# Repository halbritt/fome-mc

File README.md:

# `fome-mc` — Integrated FOME-Native Motorcycle ECU

For current assembly sourcing, clearance and ignition-copper changes, see the [manufacturing notes](docs/MANUFACTURING.md).

**`fome-mc`** is a single-PCB, 4-layer (`162.0 mm × 115.0 mm`), pottable motorcycle engine control unit running [FOME (`fome-fw`)](https://github.com/halbritt/fome-fw) on an `STM32H753ZIT6` / `STM32H743ZIT6` paired with **two onboard `STM32F042K6T6` Bosch LSU 4.9 wideband controllers**, **four 400 V / 30 A ignition IGBTs**, **four 5 V logic ignition outputs**, **four high-Z injector drivers**, **dual 4-wire stepper drivers (`DRV8825` + `2× TLE9201SG`)**, **dual `MAX9924` adaptive VR conditioners**, **soldered 4 GB industrial SDNAND logging (`CSNP32GCR01-AOW`)**, **onboard `ATWINC1500-MR210UB` U.FL Wi-Fi**, and **dual 35-pin TE Connectivity AMPSEAL (`776163-1` Black & `776163-2` Natural) sealed harness headers**.

The primary reference application is the **2007 Suzuki SV650 (K7)** (`645 cc` 90° V-twin, odd-fire `270° / 450°`, dual spark plugs per cylinder = 4 plugs total, `24-2` crank VR trigger, camless `VVT_MAP_V_TWIN` intake-MAP phase sync, dual 4-wire steppers for `ISC` idle and `STVA` secondary throttle blades, and dual Bosch LSU 4.9 wideband O2 sensors).

---

## Documentation & Visual Index

| Document / Artifact | Description |
| :--- | :--- |
| [**`docs/WIRING_SV650_K7.md`**](docs/WIRING_SV650_K7.md) | Complete 2007 Suzuki SV650 (K7) adapter harness build guide, stock 2×34-pin ECM cavity key, mating TE AMPSEAL connector BOM, pin-by-pin `J1`/`J2` cross-reference, 2-coil vs. 4-coil Primary+Trailing ignition wiring, and dual Bosch LSU 4.9 pinouts |
| [**`docs/POTTING_AND_ENCLOSURE.md`**](docs/POTTING_AND_ENCLOSURE.md) | CNC enclosure stackup, faceplate/bulkhead cutouts, `10.44 W` continuous / `12.74 W` peak thermal dissipation budget, thermal gap-pad coupling, single-pour flood potting (external GM/Delphi 1-bar baro, `FOMEMC-1`), `U29` U.FL RF shield sealing (`FOMEMC-2`), and post-potting DFU recovery |
| [**`docs/TELEMETRY_AND_RACECHRONO.md`**](docs/TELEMETRY_AND_RACECHRONO.md) | `CAN1` motorsport telemetry pod (`ESP32-S3` + `25 Hz` GPS + `Bosch MM5.10` / `BMI088` 6-axis IMU + brake/suspension ADC), `FOME_CAN_verbose.dbc` (`0x200..0x207` @ 50 Hz), RaceChrono Pro BLE DIY integration, and Insta360 / DJI Action camera sync (`FOMEMC-4`) |
| [**`docs/DESIGN.md`**](docs/DESIGN.md) | Complete electrical architecture, circuit-block reuse/adaptation ledger, power tree, and STM32H753 resource mapping |
| [**`docs/VALIDATION.md`**](docs/VALIDATION.md) | Automated ERC/DRC/Parity/Gerber/JLCPCB DFM verification ledger and pre-engine hardware bring-up checklist |
| [**`docs/SHEET_CONTRACTS.md`**](docs/SHEET_CONTRACTS.md) | Per-sheet hierarchical pin contracts (`contracts/*.interface.json`, `633` invariants across 15 sheets / 21 instances) and cross-block coupling resolution (`FOMEMC-22`) |
| [**`docs/BLOCK_LIBRARY.md`**](docs/BLOCK_LIBRARY.md) | Reference circuit-block library capture plan and provenance inventory across `fome-mc` subsheets |
| [**`docs/SEEDED_DEFECT_BENCHMARK.md`**](docs/SEEDED_DEFECT_BENCHMARK.md) | Seeded hardware defect benchmark catalog derived from `FOMEMC-1..27` design and layout remediations |
| [**`toolchain/README.md`**](toolchain/README.md) & [**`toolchain/ROUTING.md`**](toolchain/ROUTING.md) | Reproducible KiCad 10 / `kicad-happy` / `ngspice` check runner and `kicad-route` PCB routing workflow |
| [**`docs/schematics/fome-mc-schematics.pdf`**](docs/schematics/fome-mc-schematics.pdf) | Full 21-sheet hierarchical schematic PDF (plus individual sheet SVGs in [`docs/schematics/`](docs/schematics/)) |
| [**`docs/renders/fome-mc-pcb-layers.pdf`**](docs/renders/fome-mc-pcb-layers.pdf) | Multi-page PCB layer plot PDF (`F.Cu`, `In1.Cu`, `In2.Cu`, `B.Cu`, `F.Silkscreen`, `B.Silkscreen`, `F.Fab`, `Edge.Cuts`) |
| [**3D board renderings**](docs/renders/3d/fome-mc-3d-isometric.png) | High-resolution [top](docs/renders/3d/fome-mc-3d-top.png), [bottom](docs/renders/3d/fome-mc-3d-bottom.png) and [isometric](docs/renders/3d/fome-mc-3d-isometric.png) views, with [source and model provenance](docs/renders/3d/render-manifest.json) |
| [**`io-map.csv`**](io-map.csv) | Machine-verified 92-row master pinout CSV (`J1-1..35`, `J2-1..35`, and 22 internal MCU/WBO/SDNAND/Wi-Fi/power buses) |
| [**`export/BOM-fome-mc.csv`**](export/BOM-fome-mc.csv), [**`export/CPL-fome-mc.csv`**](export/CPL-fome-mc.csv) & [**`fab-manifest.json`**](reports/toolchain/fab-manifest.json) | JLCPCB PCBA Bill of Materials (`494` populated parts across `102` lines), component placement centroids, and SHA-256 fabrication package manifest (`FOMEMC-21`, `FOMEMC-24`) |
| [**`CHANGELOG.md`**](CHANGELOG.md) | Engineering decision history, schematic/PCB integration milestones, and upstream bug fixes |

---

## System Architecture

```mermaid
flowchart TB
    subgraph J1["J1 — TE AMPSEAL 35-Pin (Black 776163-1): Power & High-Current Outputs"]
        J1_PWR["+12V_IGN_SW (J1-26)<br/>+12V_MR (J1-24, J1-27)<br/>Perm_Live (J1-28)<br/>WBO1/2_H- (J1-23, J1-25)"]
        J1_INJ["INJ1..INJ4 (J1-1..4)<br/>4x High-Z Injector LS"]
        J1_IGBT["IGBT1..IGBT4 (J1-6..9)<br/>4x 400V 30A Dumb Coil IGBTs"]
        J1_AUX["AUX_LS1..4 (J1-10..13)<br/>Fuel Pump, Fan, PAIR, Tach<br/>MAIN_RLY LS (J1-14)"]
        J1_MOT["ETB1+/- & ETB2+/- (J1-15..18)<br/>STEP_1A/1B/2A/2B (J1-19..22)"]
        J1_DFU["USB_VBUS / +12V DFU (J1-35)<br/>5V_SENSOR_1/2 (J1-29..30)<br/>Unified GND (J1-5, J1-31..34)"]
    end

    subgraph J2["J2 — TE AMPSEAL 35-Pin (Natural 776163-2): Sensors, Wideband Cells & Comms"]
        J2_ANA["CLT, IAT, TPS1, TPS2_STPS,<br/>MAP1_FRONT, AV3_BARO_MAP2,<br/>AV5_TIPOVER, AV6_GEAR (J2-1..8)"]
        J2_KNK["KNOCK1 & KNOCK2 (J2-9..10)"]
        J2_TRG["VR1+/- & VR2+/- (J2-11..14)<br/>HALL1..3 & DIN1 (J2-15..18)"]
        J2_WBO["WBO1 LSU 4.9 (J2-19..22)<br/>WBO2 LSU 4.9 (J2-30..33)"]
        J2_IGN["IGN1_LOG..IGN4_LOG (J2-23..26)<br/>DASH_TECH 7800-Baud (J2-27)"]
        J2_COM["CAN1_H/L (J2-28..29, 500 kbps)<br/>USB_D+/D- (J2-34..35)"]
    end

    subgraph PCB["fome-mc 4-Layer Integrated Motorcycle ECU PCB (162.0 mm × 115.0 mm)"]
        PSU["Power Supply & Keep-Alive (psu.kicad_sch + Keep_Alive.kicad_sch)<br/>D20/D21 B340A Diode-OR (12V_IGN_SW + 12V_MR -> 12V_RAW)<br/>SMCJ24A (D1/D22) Unidirectional TVS • AO4485 Reverse PMOS + BZT52C12<br/>L1/C6 Input Filter -> LMR16020PDDAR 60V 5V Buck • 2x TLS115D0E<br/>TLV75733PDBVR 3.3V LDO • MIC5205 VBAT (U41) • 2x MCP2551 (U4 CAN1, U5 CAN2)"]
        MCU["Main ECU Brain (sheets/mcu.kicad_sch)<br/>STM32H753ZIT6 (U26, 480 MHz Cortex-M7)<br/>CSNP32GCR01-AOW 32Gbit (4GB) SDNAND (U25, SDMMC1)<br/>ATWINC1500-MR210UB U.FL Wi-Fi (U29, SPI4 PE2..PE6 + PC13)<br/>LPS25HBTR Baro (U24 DNP, I2C2) • REF3333 Fixed 3.30V VREF+ (U23)"]
        AFE["Analog, Knock & VR Front-End<br/>MCP6004 Buffers + 2.7k 0.1% Pull-Ups<br/>2x MAX9924UAUB+ VR Conditioners (U13, U14 Mode A2)<br/>Active Bandpass Knock Filter (PF4/PF5 ADC3)"]
        DRV["Power & Motion Drivers<br/>4x MIC4427 (U42..U45 in ign1/ign2) + 4x FGD3040G2-F085 IGBTs (Q201..Q204)<br/>6x VNLD5090 Dual Low-Side (U1001..U1202) + 3x 74HCT125D (U1003..U1203) + BTS716G HS (U40)<br/>2x TLE9201SG 6A H-Bridge (U201, U203) + DRV8825 Stepper (U202)"]
        WBO["Dual Onboard LSU 4.9 Wideband Controllers<br/>WBO1 (U302 STM32F042, 0x190) & WBO2 (U402 STM32F042, 0x192)<br/>MCP6004 + AD8628 + REF3033 + VND14NV04 + TJA1051T/3 (U307/U407)<br/>Internal 500 kbps CAN2 Bus (PB12/PB13) + H7 Reset/BOOT0 (PD4..PD7)"]
    end

    J1_PWR --> PSU
    PSU --> MCU & AFE & DRV & WBO
    J2_ANA & J2_KNK & J2_TRG --> AFE --> MCU
    J2_WBO <--> WBO
    J1_PWR --> WBO
    WBO <==>|"Internal CAN2 (500 kbps)<br/>+ PD4..PD7 NRST/BOOT0"| MCU
    MCU --> DRV
    DRV --> J1_INJ & J1_IGBT & J1_AUX & J1_MOT & J2_IGN
    J2_COM & J1_DFU <--> MCU
```

---

## Hardware Capabilities at a Glance

| Subsystem | Hardware Implementation | Connectors / MCU Pins | Key Ratings & Notes |
| :--- | :--- | :--- | :--- |
| **Main MCU** | `STM32H753ZIT6` (`U26`, LQFP-144, `C730207`) | 8 MHz HSE (`Y1`, `C115962`), `REF3333AIDBZR` (`REF3033`-class) fixed `3.30 V` `VREF+` (`U23`, `C130016`) | 480 MHz Cortex-M7, 2 MB Dual-Bank Flash, 1 MB RAM. Fixed `3.30 V` `VREF+` means ADC inputs are not ratiometric to `5V_SENSOR_x`; scale by `5V_SENSE_DIVIDED` (`U26.50` / `PF12` / `EFI_ADC_17`, fed by `R118 = 10 kΩ / R119 = 10 kΩ` from `/5V_SENSOR_1`) during cranking sag |
| **Onboard Logging (`FOMEMC-3`, `FOMEMC-19`)** | `CSNP32GCR01-AOW` (`U25`, `6×8 mm` LGA-8, `C2841139`) + `C113` (`4.7 µF` `C19666`) & `C114` (`100 nF` `C161115`) `< 2.0 mm` from Pin 4 (`VDD`) | `SDMMC1` 4-bit bus (`PC8..PC12, PD2`) | 4 GB (32 Gbit) soldered pottable SD NAND (`~161 hrs` @ 50 Hz / `~80 hrs` @ 100 Hz) with automatic oldest-`.mlg` ring-buffer pruning; pin-compatible with `MKDV32GCL-STH` (`C5199868`) / `XTSD32GLGEAG` |
| **Onboard Wi-Fi (`U.FL`, `FOMEMC-2`, `FOMEMC-18`, `FOMEMC-27`)** | `ATWINC1500-MR210UB` (`U29`, `C1558698` at `(166.0, 131.35 mm, 90°)`, `14.73 × 21.72 mm` `DS70005304F` footprint + `C111 = 10 µF` `C96446` & `C112 = 10 nF` `C344025` on Pin 24 `1P3V_TP`) | `SPI4` (`PE2=SCK`, `PE5=MISO`, `PE6=MOSI`, `PE4=CS`, `PE3=IRQ`, `PC13=RST`) | Enables wireless TunerStudio TCP server (`port 29000`) and built-in HTTP port `80` web server for browsing/downloading `.mlg` logs & streaming `.zip` archives; `3.7 × 3.7 mm` `Pad 29` GND paddle with 2×2 thermal/GND vias; U.FL pigtail exits aluminum enclosure |
| **`CAN1` Motorsport Telemetry (`FOMEMC-4`)** | `MCP2551-I-SN` (`U4`, `C7376`) + `PESD1CAN-UX` (`D4`, `C907839`) + `120 Ω` (`R9`, `C22787`) + `10 Ω` (`R7`, `C22859`) | `J2-28` (`CAN1_H`), `J2-29` (`CAN1_L`), `PD1` (`FDCAN1_TX`), `PD0` (`FDCAN1_RX`) | `500 kbps` external CAN1 bus: broadcasts `FOME_CAN_verbose.dbc` (`0x200..0x207`) at **`50 Hz` (`20 ms`, `canSleepPeriodMs = 20`)** and ingests **Bosch `MM5.10` 6-axis IMU** frames (`0x174`, `0x178`, `0x17C`; RaceChrono Pro decodes all 6 axes, while FOME `can_imu.cpp` logs `YawRate` and `Accel{Lat,Lon,Vert}` into `.mlg`) |
| **Wideband O2 #1 & #2 (`FOMEMC-26`)** | `2× STM32F042K6T6` (`U302`, `U402`, `C69216`) + `2× MCP6004` (`C50282`) + `2× AD8628` (`C29309`) + `2× REF3033` (`C36658`) + `2× VND14NV04` (`Q301`, `Q401`, `C2649436`) + `2× TJA1051T/3` (`U307`, `U407`, `C38695`) | `J1-23` (`WBO1_H-`), `J1-24` (`+12V_MR`), `J1-25` (`WBO2_H-`), `J2-19..22` (`WBO1`), `J2-30..33` (`WBO2`) | Internal `CAN2` (`PB12/PB13` @ 500 kbps via `U5` `MCP2551-I-SN` to `U307/U407` `TJA1051T/3`). Strapped addresses: `WBO1` = `0x190/0x191`, `WBO2` = `0x192/0x193`. H7 controls `NRST`/`BOOT0` via `PD4..PD7`. `/WBO1_H-` (`Q301` Pad 2 -> `J1-23`) and `/WBO2_H-` (`Q401` Pad 2 -> `J1-25`) use wide (`>= 1.50 mm`) low-resistance copper buses (`<= 0.05 Ω` trace resistance/ch, `< 0.13 W` loss @ `1.6 A RMS`, `< 0.45 W` @ `3.0 A` cold-start peak) |
| **High-Current Ignition (`FOMEMC-16`, `FOMEMC-19`)** | `4× FGD3040G2-F085` IGBTs (`Q201..Q204`, TO-252, `C606124` in `/ign_igbt/`) driven by `2× MIC4427` (`U42, U43`, `C461590` in `/ign1/`) | `J1-6..9` (`PB3`, `PG15`, `PG14`, `PG13`) | `380–400 V` internal collector-gate SCIS clamp, `30 A`, `250 mJ`; dedicated `HV_IGN` netclass (`0.50 mm` min copper clearance, `1.20 mm` nominal track width across all 4 copper layers `F.Cu`, `In1.Cu`, `In2.Cu`, `B.Cu`); `10 kΩ` (`R205..R208`) gate-emitter bleeders |
| **5V Logic Ignition** | `2× MIC4427` (`U44, U45`, `C461590` in `/ign2/`) 1.5 A dual push-pull buffers + `100 Ω` (`R112..R115`, `C17408`) series protection | `J2-23..26` (`PG12`, `PG11`, `PG10`, `PG9`) | Drives 4 channels (`IGN1_LOG..IGN4_LOG` on `/IGN5../IGN8`) for 3/4-wire smart coils or external igniters; `IGBT3/4` and `IGN3/4_LOG` support independent **Trailing Spark** |
| **Fuel Injectors (`FOMEMC-13`, `FOMEMC-17`)** | `2× VNLD5090TR-E` dual protected low-side (`U1001`, `U1002`, `C222209`) + `74HCT125D` (`U1003`, `C5962`) `+5V` CMOS buffer (`D201..D204` **DNP**) | `J1-1..4` (`PG5`, `PG6`, `PG7`, `PG8`) | 4 channels (`INJ1..4`), `4.9 V` gate drive (`U1003`); `D201..D204` (`B340A-13-F`, `C85098`) marked **DNP** (`exclude_from_bom`, `dnp`) so `VNLD5090TR-E` demagnetizes high-Z injectors via its internal **`42 V` active Zener clamp** (`~0.83 ms` turn-off vs `~4.8 ms` with a `14 V` Schottky clamp, preventing nonlinear fuel delivery & AFR skew at `10,500 RPM`) |
| **Aux Low-Side, Main Relay & High-Side (`FOMEMC-13`, `FOMEMC-14`, `FOMEMC-17`, `FOMEMC-25`)** | `4× VNLD5090TR-E` (`U1101..U1202`, `C222209`) + `2× 74HCT125D` (`U1103`, `U1203`, `C5962`) `+5V` CMOS buffers + `D205..D209` (`B340A-13-F`, `C85098`) + `BTS716G` (`U40`, `C85135`, spare) | `J1-10..13` (`LS5..LS8`: `PC6, PC7, PA15, PD3`), `J1-14` (`MAIN_RLY` via `PE0` -> `U1203` -> `U1202.6` + `D209` flyback), `J2-27` (`LS14` / `DASH_TECH` via `PB9` -> `U1203` -> `U1201.8`) | `D205..D209` (`B340A-13-F`, `C85098`) populated for inductive solenoids/relays (`/LS5../LS8`, `/MAIN_RLY` on `J1-14`); `J1-13` (`/LS8` / `AUX_LS4` Tach) includes `R212 = 2.2 kΩ` (`C4190`) pull-up to `/12V_MR` (`J2-27` `DASH_TECH` is open-drain low-side; uses cluster/harness pull-up) |
| **Idle Stepper (`ISC`)** | `DRV8825PWPR` (`U202`, HTSSOP-28, `C81582`) bipolar microstepping driver | `J1-19..22` (`STEP_1A/1B/2A/2B`), `PB4` (`STEP`), `PB7` (`DIR`), `PB8` (`~EN`) | Regulated `0.77 A` chopper limit (`R213, R214 = 0.20 Ω` `1206` sense `C25335`, `VREF = 0.767 V` via `R215 = 33 kΩ` `C25779` / `R216 = 10 kΩ` `C25744` from `+3V3`) for SV650 4-wire `ISC` idle valve |
| **Secondary Throttle (`STVA`) / Dual ETB** | `2× TLE9201SG` (`U201` in `/etb1/`, `U203` inline in `/stepper_etb/`, PG-DSO-12, `C2653438`) 6 A H-bridges | `J1-15..18` (`ETB1_OUT+/-`, `ETB2_OUT+/-`), `PD12/PD10/PD11` (`ETB1` `PWM/DIR/DIS`), `PD13/PD9/PD8` (`ETB2` `PWM/DIR/DIS`) | Drives SV650 4-wire `STVA` secondary throttle stepper or dual DC drive-by-wire throttles |
| **Crank/Cam VR & Hall (`FOMEMC-25`)** | `2× MAX9924UAUB+` (`U13, U14`, `LCSC C143633`) differential adaptive VR conditioners + `SN74LVC2G17DB` (`U8, U9, U10`, `C10429`) +3V3 Hall buffers + `SRV05-4` (`U11, U12`, `C85364`) ESD arrays | `J2-11..14` (`VR1+`/`VR1-` -> `PE14`, `VR2+`/`VR2-` -> `PE15`), `J2-15..18` (`DIGITAL_1..4` -> `PG1, PG0, PE11, PE10`) | Wired in **Mode A2 (Internal Adaptive Peak Threshold + Internal Bias + Zero-Crossing Watchdog Enabled)**: Pin 6 (`ZERO_EN`) = `GND`, Pin 9 (`INT_THRS`) = `GND`, Pin 4 (`BIAS`) = `GND` (`2.5 V` internal bias via `R35..R38 = 10 kΩ`), Pin 8 (`EXT`) = `NC`; `C38, C39` (`100 nF` `0603` `C161115`) `< 2 mm` from Pin 10 (`VCC = /5V_SENSOR_1`) in parallel with `C109, C110`; `R23..R28 = 2.7 kΩ` (`C705760`) pull-ups to `/5V_SENSOR_1` and `R29..R34 = 2.7 kΩ` (`C705760`) series input resistors on `DIGITAL_1..6` |
| **Analog, Baro (`FOMEMC-1`), Gear (`FOMEMC-14`), Temp & Knock** | `MCP6004` buffers (`U7, U15, U17, U19, U21`, `C50282`) + `SRV05-4` TVS arrays (`U16, U18, U20, U22`, `C85364`) | `J2-1..8` (`PC1, PC2, PA1, PA3, PA0, PA2, PA4, PA5`), `J2-9..10` (`PF4, PF5` `ADC3`) | `2.7 kΩ 0.1%` (`C705760`) bias to `/5V_SENSOR_1` on `AT1`/`AT2` (`CLT`/`IAT`); **`R219 = 1.5 kΩ 1%` (`C22843`) pull-up to `/5V_SENSOR_1` on `AV6_GEAR` (`J2-8`, `PA5`)** (`0.87–3.19 V` at `PA5` after `+5V` `U19` buffer and `5.6 kΩ / 10 kΩ` divider); **`J2-6` (`PA2` / `EFI_ADC_2`) defaults to external `MT_GM_1_BAR` (`GM 12614970` / `Delphi PS10150` `10–105 kPa`) barometer** for single-pour flood potting (`U24` `LPS25HBTR` DNP); active bandpass knock filter (`U7`) on `PF4`/`PF5` |
| **Power Supply, Brownout & `VBAT` `BKPSRAM` Keep-Alive (`FOMEMC-15`, `FOMEMC-17`, `FOMEMC-25`)** | `D20/D21` (`B340A-13-F`, `C85098`) diode-OR + `SMCJ24A` (`D1, D22`, `C224045`) TVS + `AO4485` (`Q1`, `C51499`) PMOS reverse block + `C4` (`4.7 µF 50 V X7R 1210` `C417122`) + `L1/C6` (`47 µF` polymer `C454346`) filter + `LMR16020PDDAR` (`U3`, `C190006`, 60 V 2 A 5V buck) + `C2, C5, C7` (`1 µF 50 V X7R 0805` `C354368`) + `C12` (`10 µF 25 V X5R 0603` `C96446`) + `2× TLS115D0E` (`U1, U2`, `C3747428`) + `TLV75733PDBVR` (`U6`, `C485517`, 3.3 V 1 A LDO) + `MIC5205-3.3YM5` (`U41`, `C37970` `VBAT` via `D16/D17` + `D6/D7/D8` `B5819W` `C8598` + `BT1` DNP) | `J1-26` (`+12V_IGN_SW`), `J1-24/27` (`+12V_MR`), `J1-28` (`Perm_Live`), `J1-29..30` (`5V_SENSOR_1/2`), `J1-5, 31..34` (`GND`) | Boots on `J1-26` (`+12V_IGN_SW`, sensed on `PC5`) and latches `/12V_MR` (`J1-27`) via `PE0` -> `J1-14` (`MAIN_RLY`). `U3` (`LMR16020`) has a `4.30 V` minimum operating `VIN`, and `U6` (`TLV75733`, `0.25 V` max dropout) regulates `+3V3` down to `VIN = 4.30 V` (**`V_BATT ≈ 4.8 V` steady-state floor** across `D20/D21 + Q1 + L1`, with `C1 + C6 = 2 × 47 µF` riding through sub-ms cranking dips). `PC14/PC15` on `U26` are `no_connect` (no LSE crystal), so `VBAT` (`U41` -> `D17` -> `D7` into `U26.6`) retains the **`4 KB BKPSRAM` and 32 `RTC_BKPxR` registers** across key-off |
| **PCB Mechanical & Mounting (`FOMEMC-27`)** | `162.0 mm × 115.0 mm` 4-layer FR-4 TG170 (`Edge.Cuts` `X = 26..188`, `Y = 25..140`) + **`4× M4` (`Ø 4.3 mm` NPTH) corner mounting holes `H1..H4`** | `H1` `(30.0, 29.0)`, `H2` `(184.0, 29.0)`, `H3` `(30.0, 136.0)`, `H4` `(184.0, 136.0)` | `154.0 mm × 107.0 mm` hole centers (`4.0 mm` inset from board corners) for `M4×10` enclosure baseplate bosses; `514` total board footprints (`494` populated SMT + `16` DNP + `4` `H1..H4` mounting holes) |
| **Post-Potting Recovery** | Dual-threshold `J1-35` (`USB_VBUS_BOOT0`) + `PD4..PD7` | `J1-35`, `J2-34` (`USB_D+`), `J2-35` (`USB_D-`), `J2-28..29` (`CAN1`) | `+5 V` on `J1-35` = normal USB/RusEFI/MSD (`R217 = 10 kΩ / R218 = 12 kΩ` + `D211 = B5819W` `C8598` into `PA9`); `+12 V` on `J1-35` conducts `D210` (`BZT52C6V8` `C173404`, `6.8 V` Zener) + `R209 = 12 kΩ` (`C25752`) override to assert `STM32H753 BOOT0 = 1` (`0483:df11` ROM DFU) through the sealed harness |

---

## Dual 35-Pin TE AMPSEAL Connector Pinout (`J1` & `J2`)

For full pin-by-pin wiring tables, wire gauges, crimp terminal part numbers, and 2007 Suzuki SV650 (K7) ECM (`34-pin` + `34-pin`) cross-references, see [**`docs/WIRING_SV650_K7.md`**](docs/WIRING_SV650_K7.md) and [**`io-map.csv`**](io-map.csv).

---

## PCB Layout & Layer Renderings

````carousel

<!-- slide -->

<!-- slide -->

<!-- slide -->

<!-- slide -->

````

### 3D Board Views

[Top](docs/renders/3d/fome-mc-3d-top.png) · [Bottom](docs/renders/3d/fome-mc-3d-bottom.png) · [Isometric](docs/renders/3d/fome-mc-3d-isometric.png)

These 4064 × 3056 PNGs use KiCad 10.0.7's high-quality ray tracer, orthographic
views, native materials and saved copper fill. They were rendered from a
snapshot without refilling or saving the source design.

The 3D assembly is incomplete: 46 of 514 footprints have no model reference (42
components including the J1/J2 connector housings, plus the 4 M4 mounting holes
H1..H4), and 12 referenced model files are unavailable.
The [render manifest](docs/renders/3d/render-manifest.json) records the board hash,
camera settings, commands, image hashes and model coverage. These images document
appearance; they do not establish mechanical clearance or electrical acceptance.

---

## Hierarchical Schematic Renderings

All 21 schematic sheets are exported as vector SVGs in [`docs/schematics/`](docs/schematics/) and compiled into a single searchable PDF at [**`docs/schematics/fome-mc-schematics.pdf`**](docs/schematics/fome-mc-schematics.pdf).

````carousel

<!-- slide -->

<!-- slide -->

<!-- slide -->

<!-- slide -->

````

---

## Repository Structure

```text
fome-mc/
├── fome-mc.kicad_pro                # KiCad 10 project configuration
├── fome-mc.kicad_sch                # Root hierarchical schematic (J1/J2 AMPSEAL headers + C1 + R219 + 20 subsheet blocks)
├── fome-mc.kicad_pcb                # 4-layer PCB layout (162.0 mm × 115.0 mm, 514 footprints incl. 4x M4 H1..H4 at 154.0 × 107.0 mm centers)
├── sym-lib-table                    # Project symbol library table (-> libs/symbols/)
├── fp-lib-table                     # Project footprint library table (-> libs/footprints/)
├── io-map.csv                       # Authoritative 70-pin J1/J2 + 22 internal net cross-reference table
├── Makefile                         # Reproducible verification & manufacturing export targets
├── README.md                        # Project overview, architecture diagrams & visual gallery
├── CHANGELOG.md                     # Detailed engineering changelog & bug-fix history
├── sheets/                          # 15 hierarchical child schematic sheets (20 child instances + root = 21 sheet instances)
│   ├── mcu.kicad_sch                # STM32H753ZIT6, 8 MHz HSE, REF3333, LPS25HB (DNP), CSNP32GCR01-AOW 4GB SDNAND (C113/C114), ATWINC1500-MR210UB Wi-Fi (C111/C112)
│   ├── psu.kicad_sch                # SMCJ24A TVS, AO4485 PMOS, C4 4.7uF 50V X7R 1210, L1/C6 filter, LMR16020 5V buck, 2x TLS115D0E, TLV75733, 2x MCP2551
│   ├── Keep_Alive.kicad_sch         # D20/D21 (B340A-13-F C85098) 12V_IGN_SW + 12V_MR diode-OR + D22 (SMCJ24A) TVS + MIC5205 (U41) VBAT 4 KB BKPSRAM keep-alive
│   ├── wbo1.kicad_sch               # Onboard Bosch LSU 4.9 Wideband Controller #1 (STM32F042 + VND14NV04 + >=1.50mm WBO1_H- bus + TJA1051T/3)
│   ├── wbo2.kicad_sch               # Onboard Bosch LSU 4.9 Wideband Controller #2 (STM32F042 + VND14NV04 + >=1.50mm WBO2_H- bus + TJA1051T/3)
│   ├── ign_igbt.kicad_sch           # 4x FGD3040G2-F085 400V 30A ignition IGBTs (Q201..Q204, HV_IGN 0.50mm clearance netclass) + 15R/10k gate network
│   ├── ign4.kicad_sch               # Dual MIC4427 4-ch driver subsheet (instantiated twice: ign1 U42/U43 for Q201..Q204 gates, ign2 U44/U45 + 100R for IGN5..8)
│   ├── stepper_etb.kicad_sch        # DRV8825PWPR stepper (U202, 0.77A) + 2nd TLE9201SG (U203 inline) + D201..D204 (DNP) & D205..D209 clamps + R212 tach pull-up + J1-35 BOOT0
│   ├── etb-9201.kicad_sch           # TLE9201SG 6A H-bridge subsheet (instantiated once: etb1 U201)
│   ├── lowside_quad.kicad_sch       # Dual VNLD5090 + 74HCT125D (C5962) 5V CMOS buffer low-side subsheet (instantiated 3x: INJ1..4, LS5..8, MAIN_RLY/DASH_TECH)
│   ├── highside_quad.kicad_sch      # BTS716G (U40 C85135) protected high-side driver
│   ├── triggers.kicad_sch           # 2x MAX9924UAUB+ (U13, U14) Mode A2 differential VR conditioners (C38/C39 + C109/C110) + SN74LVC2G17DB (U8..U10) Hall inputs
│   ├── quad_analog.kicad_sch        # MCP6004 (U17, U19, U21) buffered 0-5V analog input conditioning + SRV05-4 (U18, U20, U22) ESD (instantiated 3x)
│   ├── quad_analog_pullup.kicad_sch # Precision 2.7k 0.1% thermistor bias to 5V_SENSOR_1 & 0-5V analog inputs (MCP6004 U15 + SRV05-4 U16)
│   └── knock.kicad_sch              # 2-channel active bandpass knock conditioning (PF4/PF5 ADC3)
├── libs/
│   ├── symbols/                     # Project-local KiCad symbol libraries (.lib, .dcm)
│   └── footprints/                  # Project-local KiCad footprint libraries (.pretty)
├── docs/
│   ├── DESIGN.md                    # Complete electrical & firmware architecture specification
│   ├── VALIDATION.md                # Verification ledger, DFM/stock audit & bench bring-up procedure
│   ├── WIRING_SV650_K7.md           # 2007 Suzuki SV650 (K7) wiring harness & connector guide
│   ├── POTTING_AND_ENCLOSURE.md     # Enclosure stackup, thermal gap pads & potting guide (incl. FOMEMC-1, FOMEMC-2, FOMEMC-27)
│   ├── TELEMETRY_AND_RACECHRONO.md  # CAN1 motorsport telemetry pod, RaceChrono Pro & camera integration (FOMEMC-4)
│   ├── BLOCK_LIBRARY.md             # Reference block library capture plan & per-sheet inventory
│   ├── SHEET_CONTRACTS.md           # Per-sheet boundary contracts (FOMEMC-22)
│   ├── SEEDED_DEFECT_BENCHMARK.md   # Seeded defect benchmark catalog from FOMEMC-1..27
│   ├── renders/                     # High-resolution PNG/SVG/PDF PCB layer, floorplan & pinout renders
│   └── schematics/                  # All 21 schematic sheets in SVG + compiled fome-mc-schematics.pdf
├── export/
│   ├── fome-mc.net                  # Tracked KiCad schematic netlist (510 schematic components)
│   ├── BOM-fome-mc.csv              # JLCPCB PCBA Bill of Materials (494 populated components across 102 BOM lines with 100% LCSC coverage; 16 DNP excluded)
│   ├── CPL-fome-mc.csv              # JLCPCB PCBA Component Placement / Centroid file (494 populated components; 16 DNP + 4x M4 H1..H4 excluded)
│   └── gerbers/                     # Reproducible 4-layer Gerbers, Excellon drill files & job file (verified by reports/toolchain/fab-manifest.json)
├── scripts/
│   ├── verify_io_map.py             # Cross-checks io-map.csv against schematics, netlist, contracts, and FOME firmware
│   ├── render_docs.py               # Regenerates all schematic SVGs/PDF, PCB renders, floorplan & pinout diagrams
│   ├── export_bom_cpl.py            # Generates and validates export/BOM-fome-mc.csv and export/CPL-fome-mc.csv (FOMEMC-24)
│   └── generate_fab_package.py      # Generates and verifies export/gerbers/ and reports/toolchain/fab-manifest.json (FOMEMC-21)
├── telemetry-pod/                   # CAN1 telemetry pod KiCad project skeleton (placeholders until agent-ee generates it; FOMEMC-28)
└── toolchain/                       # Automated KiCad 10 ERC, DRC, netlist parity, Gerber & DFM check suite
```

---

## Reproducible Verification & Rendering Commands

All hardware checks and documentation renders run locally using KiCad 10 CLI (`kicad-cli`), Python 3, and `rsvg-convert`:

```bash
# 1. Verify local EDA toolchain (KiCad 10, kicad-cli, pcbnew, ngspice, freecad)
make doctor

# 2. Verify 100% pinout and sheet-contract parity across io-map.csv, schematics, netlist, contracts, and fome-fw
make verify-io

# 3. Run schematic ERC, PCB DRC, netlist extraction, manufacturing exports, and analysis
make check

# 4. Verify reproducible Gerbers, Excellon drills, netlist, BOM/CPL, and SHA-256 fab manifest against HEAD
make verify-fab-package REV=HEAD

# 5. Regenerate all 2D schematic SVGs/PDF, PCB layer plots, floorplan, and J1/J2 pinout diagrams
make renders

# 6. Render native 3D views using a populated model cache (see toolchain guide)
make render-3d
# Inspect the images and model coverage, then publish that exact run:
# make render-3d-publish RUN=build/runs/project/fome-mc/3d-renders-<stamp>
```

The [3D render toolchain guide](toolchain/README.md#3d-board-renders) documents
persistent model caches, explicit model downloads, render settings and publication
checks. Missing model references and unavailable custom models leave the 3D
assembly incomplete.

### Current Verification Status

| Gate | Result | Details |
| :--- | :--- | :--- |
| **`verify_io_map.py` (`make verify-io`)** | **PASS** | `70 / 70` `J1`/`J2` pins + `22` internal buses + `510` netlist components (`494` populated in BOM/CPL with 100% LCSC coverage after excluding `16` DNP footprints: `BT1`, `D201..D204`, `J8`, `J9`, `J11..J16`, `JP1`, `JP2`, `U24`; plus `4× M4` mounting holes `H1..H4` = `514` total board footprints) + `15` `contracts/*.interface.json` (`633` invariants) verified across `io-map.csv`, `export/fome-mc.net`, and `fome-fw` |
| **Schematic ERC (`make erc`, `FOMEMC-20`, `FOMEMC-25`)** | **PASS** | **`0` violations (`0` errors, `0` warnings)** across all 21 hierarchical schematic sheets (`U13, U14` `MAX9924UAUB+` in Mode A2; `VBAT` `4 KB BKPSRAM` keep-alive with `PC14/PC15` `no_connect`) |
| **PCB DRC (`make drc`, `FOMEMC-18`, `FOMEMC-19`, `FOMEMC-26`, `FOMEMC-27`)** | **PASS** | **`0` violations (`0` errors, `0` warnings)**, **`0` `unconnected_items`**, **`0` `schematic_parity`**, **`0` `starved_thermal`** (`min_resolved_spokes: 2`), `0` `silk_overlap`, `0` `track_dangling`, `0` `via_dangling`, `HV_IGN` `0.50 mm` clearance across all 4 copper layers (`F.Cu`, `In1.Cu`, `In2.Cu`, `B.Cu`), wide (`>= 1.50 mm`, `<= 0.05 Ω`) `/WBO1_H-` & `/WBO2_H-` heater copper buses, and `4× M4` (`Ø 4.3 mm` NPTH) corner mounting holes `H1..H4` at `(30.0, 29.0)`, `(184.0, 29.0)`, `(30.0, 136.0)`, `(184.0, 136.0)` |
| **Netlist & Analysis (`make netlist`, `make analyze`)** | **PASS** | `510` schematic components (`494` populated SMT/THT components + `16` DNP footprints + `4` `H1..H4` mounting holes = `514` board footprints), `routing_complete: true` |
| **Exports (`make export`, `make verify-fab-package`, `FOMEMC-21`, `FOMEMC-24`)** | **PASS** | Tracked `export/fome-mc.net`, `export/BOM-fome-mc.csv` (`494` populated components across `102` BOM lines with 100% LCSC coverage and 1-to-1 `(value, package) -> LCSC` mapping), `export/CPL-fome-mc.csv` (`494` populated components), `export/gerbers/` (`14` Gerber/Excellon/job files), and `reports/toolchain/fab-manifest.json` (`22` verified artifacts) |

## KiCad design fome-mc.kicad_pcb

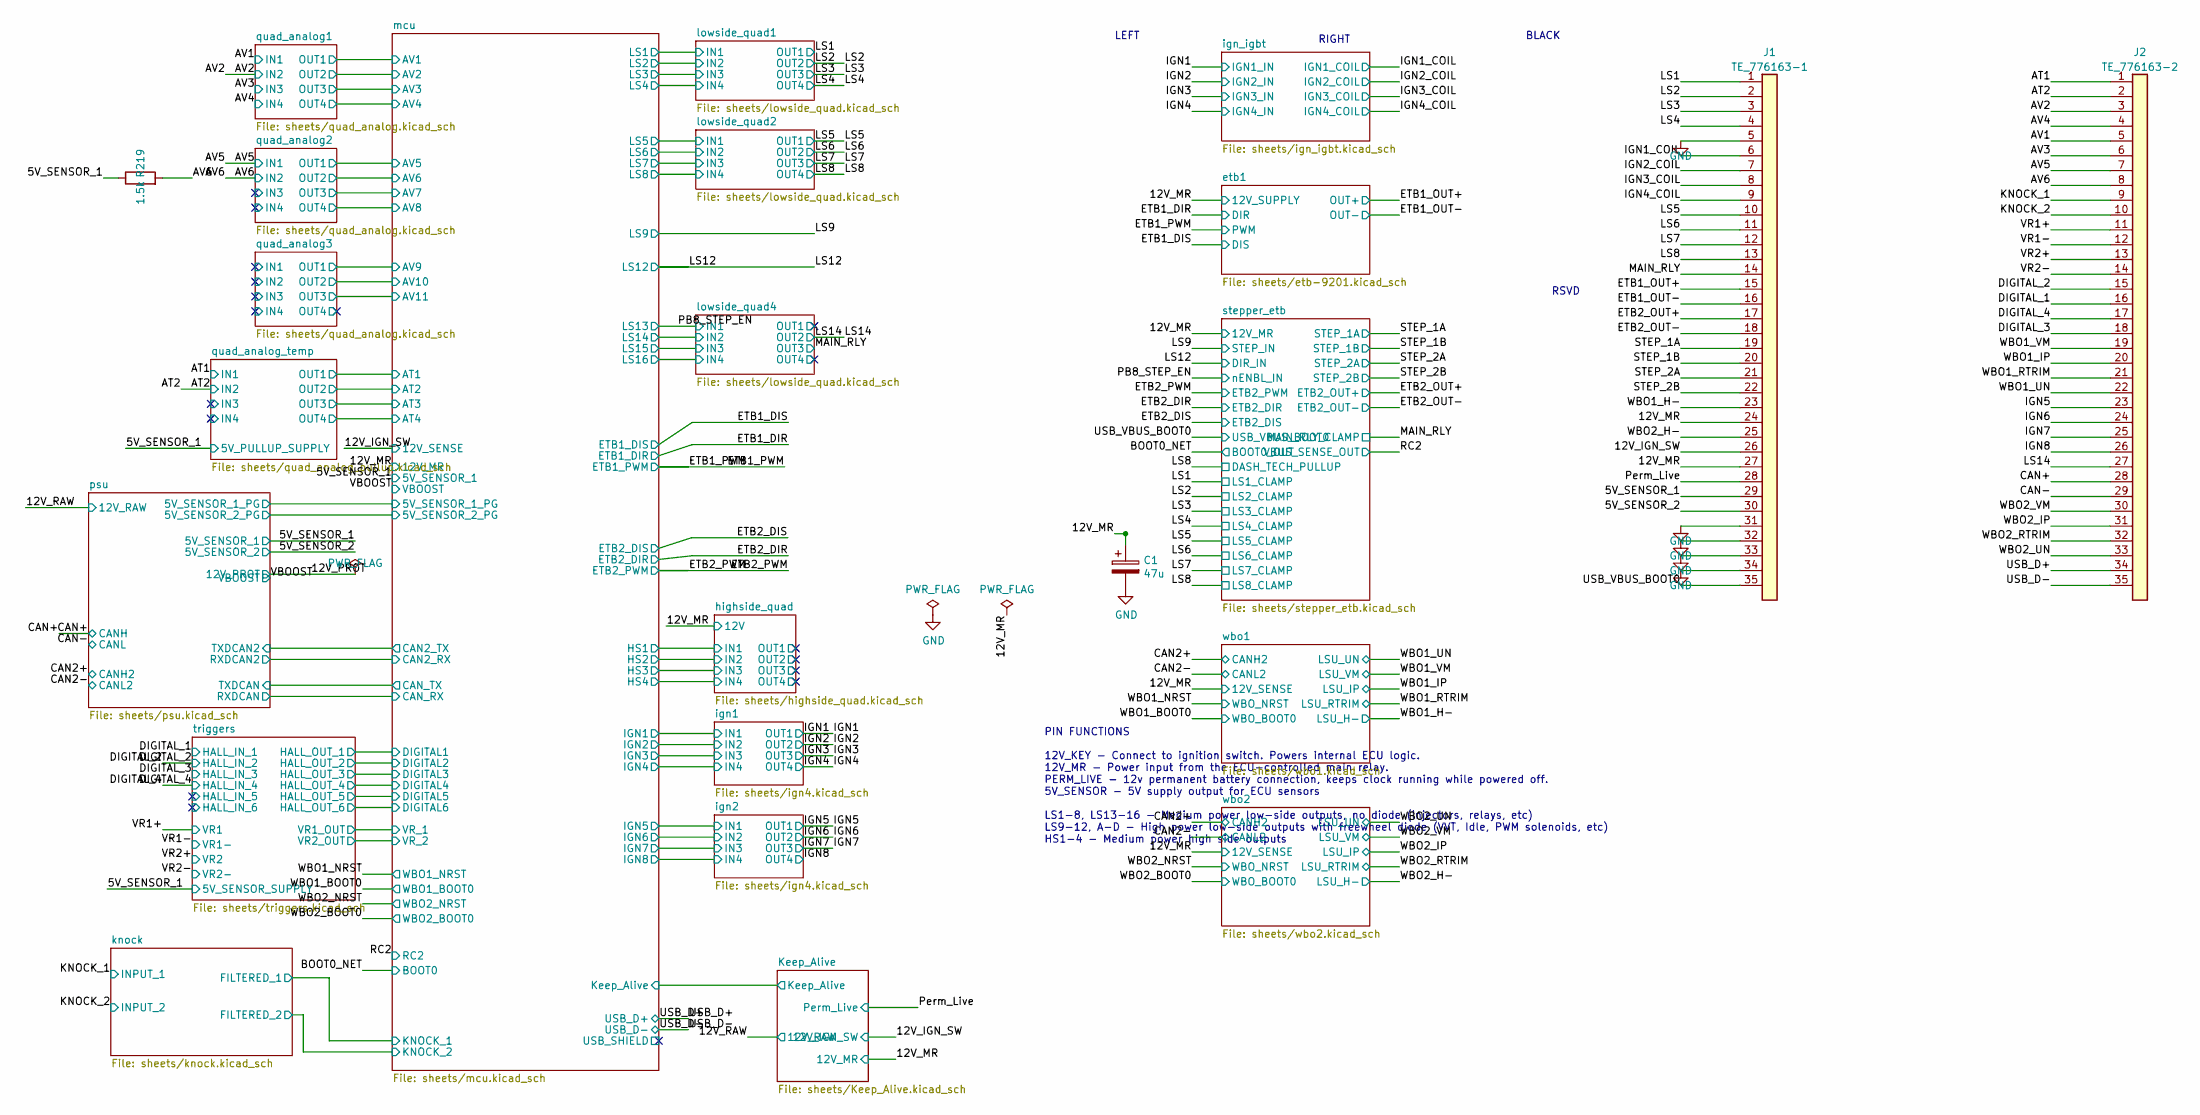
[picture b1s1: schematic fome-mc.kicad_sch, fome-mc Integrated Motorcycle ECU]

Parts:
C1: 47u; CP_Elec_8x10.5; LCSC C454346
J1: TE_776163-1; ampseal-35; LCSC C412117
J2: TE_776163-2; ampseal-35-2; LCSC C5172878
R219: 1.5k; R_0603_1608Metric; LCSC C22843

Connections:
/5V_SENSOR_1: J1.29, R219.1; also elsewhere on the board
/5V_SENSOR_2: J1.30; also elsewhere on the board
/12V_IGN_SW: J1.26; also elsewhere on the board
/12V_MR: C1.1, J1.24, J1.27; also elsewhere on the board
/AT1: J2.1; also elsewhere on the board
/AT2: J2.2; also elsewhere on the board
/AV1: J2.5; also elsewhere on the board
/AV2: J2.3; also elsewhere on the board
/AV3: J2.6; also elsewhere on the board
/AV4: J2.4; also elsewhere on the board
/AV5: J2.7; also elsewhere on the board
/AV6: J2.8, R219.2; also elsewhere on the board
/CAN+: J2.28; also elsewhere on the board
/CAN-: J2.29; also elsewhere on the board
/DIGITAL_1: J2.16; also elsewhere on the board
/DIGITAL_2: J2.15; also elsewhere on the board
/DIGITAL_3: J2.18; also elsewhere on the board
/DIGITAL_4: J2.17; also elsewhere on the board
/ETB1_OUT+: J1.15; also elsewhere on the board
/ETB1_OUT-: J1.16; also elsewhere on the board
/ETB2_OUT+: J1.17; also elsewhere on the board
/ETB2_OUT-: J1.18; also elsewhere on the board
/IGN1_COIL: J1.6; also elsewhere on the board
/IGN2_COIL: J1.7; also elsewhere on the board
/IGN3_COIL: J1.8; also elsewhere on the board
/IGN4_COIL: J1.9; also elsewhere on the board
/IGN5: J2.23; also elsewhere on the board
/IGN6: J2.24; also elsewhere on the board
/IGN7: J2.25; also elsewhere on the board
/IGN8: J2.26; also elsewhere on the board
/KNOCK_1: J2.9; also elsewhere on the board
/KNOCK_2: J2.10; also elsewhere on the board
/LS1: J1.1; also elsewhere on the board
/LS2: J1.2; also elsewhere on the board
/LS3: J1.3; also elsewhere on the board
/LS4: J1.4; also elsewhere on the board
/LS5: J1.10; also elsewhere on the board
/LS6: J1.11; also elsewhere on the board
/LS7: J1.12; also elsewhere on the board
/LS8: J1.13; also elsewhere on the board
/LS14: J2.27; also elsewhere on the board
/MAIN_RLY: J1.14; also elsewhere on the board
/Perm_Live: J1.28; also elsewhere on the board
/STEP_1A: J1.19; also elsewhere on the board
/STEP_1B: J1.20; also elsewhere on the board
/STEP_2A: J1.21; also elsewhere on the board
/STEP_2B: J1.22; also elsewhere on the board
/USB_D+: J2.34; also elsewhere on the board
/USB_D-: J2.35; also elsewhere on the board
/USB_VBUS_BOOT0: J1.35; also elsewhere on the board
/VR1+: J2.11; also elsewhere on the board
/VR1-: J2.12; also elsewhere on the board
/VR2+: J2.13; also elsewhere on the board
/VR2-: J2.14; also elsewhere on the board
/WBO1_H-: J1.23; also elsewhere on the board
/WBO1_IP: J2.20; also elsewhere on the board
/WBO1_RTRIM: J2.21; also elsewhere on the board
/WBO1_UN: J2.22; also elsewhere on the board
/WBO1_VM: J2.19; also elsewhere on the board
/WBO2_H-: J1.25; also elsewhere on the board
/WBO2_IP: J2.31; also elsewhere on the board
/WBO2_RTRIM: J2.32; also elsewhere on the board
/WBO2_UN: J2.33; also elsewhere on the board
/WBO2_VM: J2.30; also elsewhere on the board

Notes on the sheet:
LEFT
RSVD
PIN FUNCTIONS 12V_KEY - Connect to ignition switch. Powers internal ECU logic. 12V_MR - Power input from the ECU-controlled main relay. PERM_LIVE - 12v permanent battery connection, keeps clock running while powered off. 5V_SENSOR - 5V supply output for ECU sensors LS1-8, LS13-16 - Medium power low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
BLACK
RIGHT

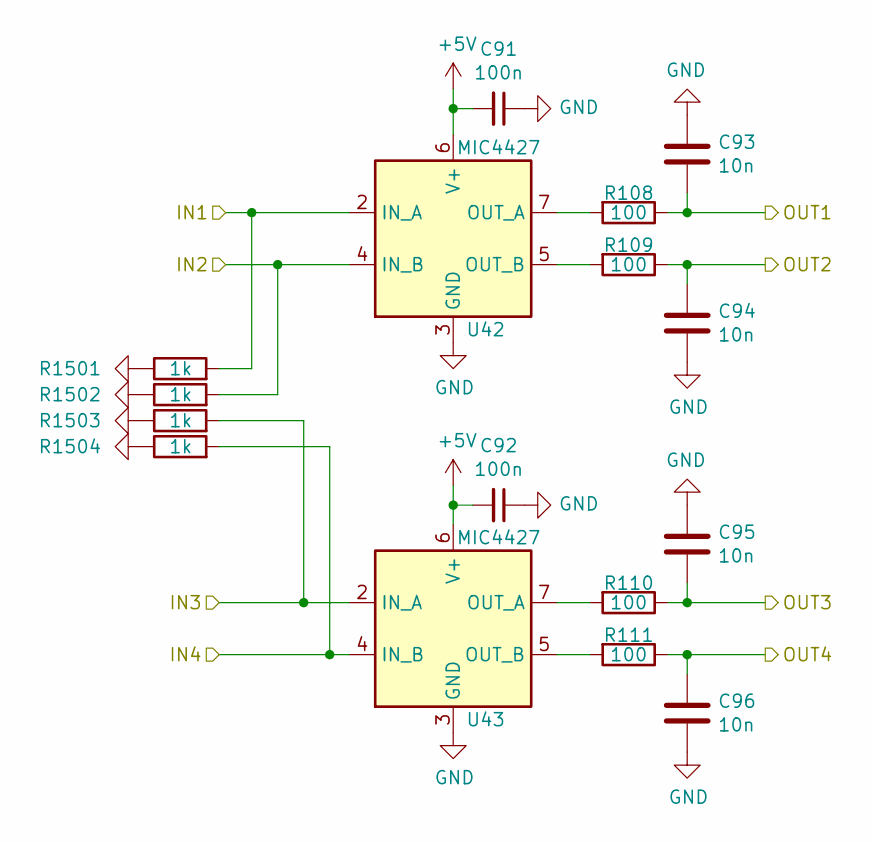
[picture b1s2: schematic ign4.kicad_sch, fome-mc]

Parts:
C91, C92: 100n; C_0603_1608Metric; LCSC C161115
C93, C94, C95, C96: 10n; C_0603_1608Metric; LCSC C344025
R108, R109, R110, R111: 100; R_0805_2012Metric; LCSC C17408
R1501, R1502, R1503, R1504: 1k; R_0402_1005Metric; LCSC C11702
U42, U43: MIC4427; SO-8_3.9x4.9mm_P1.27mm; LCSC C461590

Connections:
+5V: C91.2, C92.2, U42.6 (V+), U43.6 (V+); also elsewhere on the board
/IGN1: C93.1, R108.1; also elsewhere on the board
/IGN2: C94.1, R109.1; also elsewhere on the board
/IGN3: C95.1, R110.1; also elsewhere on the board
/IGN4: C96.1, R111.1; also elsewhere on the board
/ign1/IN1: R1501.2, U42.2 (IN_A); also elsewhere on the board
/ign1/IN2: R1502.2, U42.4 (IN_B); also elsewhere on the board
/ign1/IN3: R1503.2, U43.2 (IN_A); also elsewhere on the board
/ign1/IN4: R1504.2, U43.4 (IN_B); also elsewhere on the board
unnamed: R108.2, U42.7 (OUT_A)
unnamed: R109.2, U42.5 (OUT_B)
unnamed: R110.2, U43.7 (OUT_A)
unnamed: R111.2, U43.5 (OUT_B)

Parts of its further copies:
C97, C98: 100n; C_0603_1608Metric; LCSC C161115
C99, C100, C101, C102: 10n; C_0603_1608Metric; LCSC C344025
R112, R113, R114, R115: 100; R_0805_2012Metric; LCSC C17408
R1601, R1602, R1603, R1604: 1k; R_0402_1005Metric; LCSC C11702
U44, U45: MIC4427; SO-8_3.9x4.9mm_P1.27mm; LCSC C461590

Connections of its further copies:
+5V: C97.2, C98.2, U44.6 (V+), U45.6 (V+); also elsewhere on the board
/IGN5: C99.1, R112.1; also elsewhere on the board
/IGN6: C100.1, R113.1; also elsewhere on the board
/IGN7: C101.1, R114.1; also elsewhere on the board
/IGN8: C102.1, R115.1; also elsewhere on the board
/ign2/IN1: R1601.2, U44.2 (IN_A); also elsewhere on the board
/ign2/IN2: R1602.2, U44.4 (IN_B); also elsewhere on the board
/ign2/IN3: R1603.2, U45.2 (IN_A); also elsewhere on the board
/ign2/IN4: R1604.2, U45.4 (IN_B); also elsewhere on the board
unnamed: R112.2, U44.7 (OUT_A)
unnamed: R113.2, U44.5 (OUT_B)
unnamed: R114.2, U45.7 (OUT_A)
unnamed: R115.2, U45.5 (OUT_B)

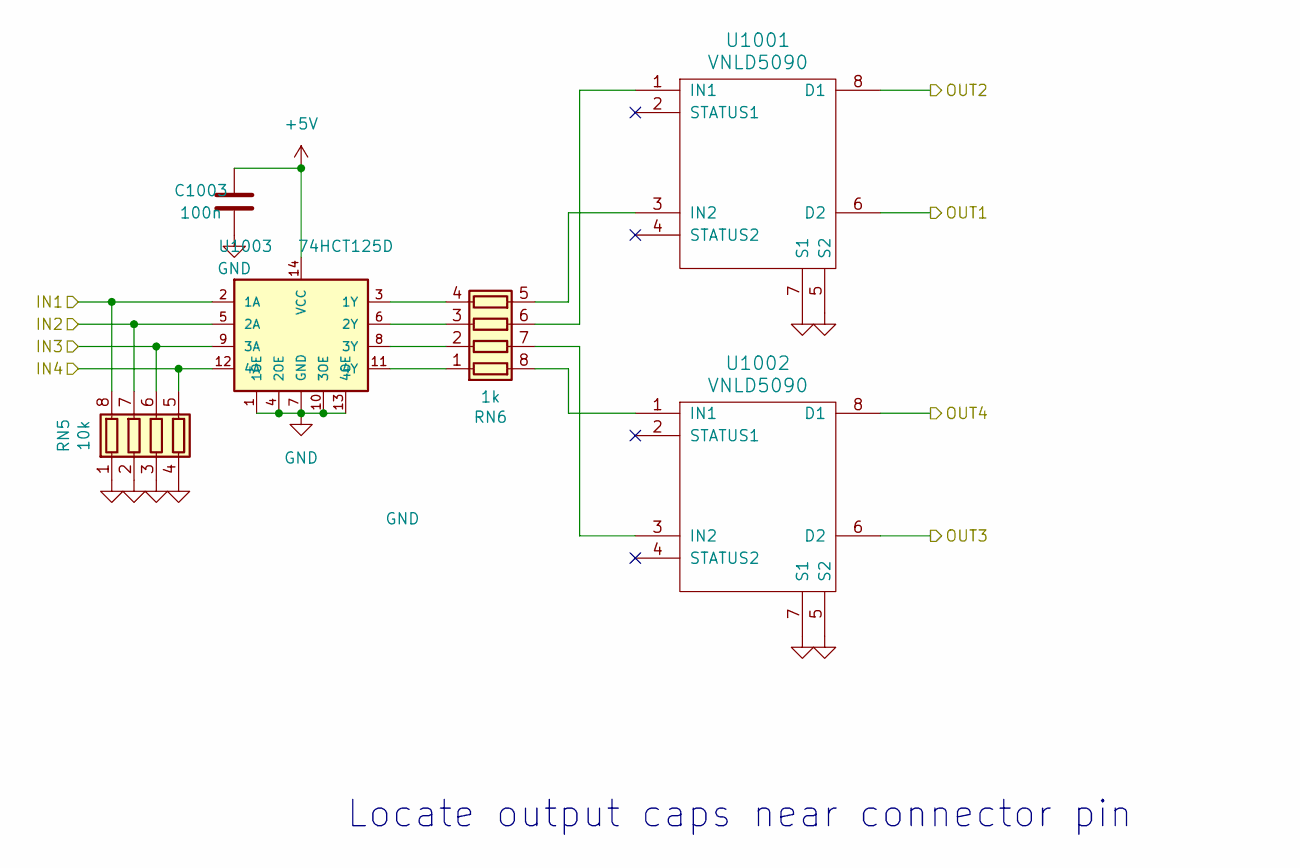
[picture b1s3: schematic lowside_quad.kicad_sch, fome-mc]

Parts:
C1003: 100n; C_0603_1608Metric; LCSC C161115
RN5: 10k; R_Array_Convex_4x0603; LCSC C29718
RN6: 1k; R_Array_Convex_4x0603; LCSC C20197
U1001, U1002: VNLD5090; SOIC-8_3.9x4.9mm_P1.27mm; LCSC C222209
U1003: 74HCT125D; SOIC-14_3.9x8.7mm_P1.27mm; LCSC C5962

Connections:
+5V: C1003.1, U1003.14 (VCC); also elsewhere on the board
/LS1: U1001.6 (D2); also elsewhere on the board
/LS2: U1001.8 (D1); also elsewhere on the board
/LS3: U1002.6 (D2); also elsewhere on the board
/LS4: U1002.8 (D1); also elsewhere on the board
/lowside_quad1/IN1: RN5.8 (R1.2), U1003.2 (1A); also elsewhere on the board
/lowside_quad1/IN2: RN5.7 (R2.2), U1003.5 (2A); also elsewhere on the board
/lowside_quad1/IN3: RN5.6 (R3.2), U1003.9 (3A); also elsewhere on the board
/lowside_quad1/IN4: RN5.5 (R4.2), U1003.12 (4A); also elsewhere on the board
unnamed: RN6.1 (R1.1), U1003.11 (4Y)
unnamed: RN6.8 (R1.2), U1002.1 (IN1)
unnamed: RN6.2 (R2.1), U1003.8 (3Y)
unnamed: RN6.7 (R2.2), U1002.3 (IN2)
unnamed: RN6.3 (R3.1), U1003.6 (2Y)
unnamed: RN6.6 (R3.2), U1001.1 (IN1)
unnamed: RN6.4 (R4.1), U1003.3 (1Y)
unnamed: RN6.5 (R4.2), U1001.3 (IN2)

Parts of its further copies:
C1103, C1203: 100n; C_0603_1608Metric; LCSC C161115
RN7, RN9: 10k; R_Array_Convex_4x0603; LCSC C29718
RN8, RN10: 1k; R_Array_Convex_4x0603; LCSC C20197
U1101, U1102, U1201, U1202: VNLD5090; SOIC-8_3.9x4.9mm_P1.27mm; LCSC C222209
U1103, U1203: 74HCT125D; SOIC-14_3.9x8.7mm_P1.27mm; LCSC C5962

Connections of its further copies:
+5V: C1103.1, C1203.1, U1103.14 (VCC), U1203.14 (VCC); also elsewhere on the board
/LS5: U1101.6 (D2); also elsewhere on the board
/LS6: U1101.8 (D1); also elsewhere on the board
/LS7: U1102.6 (D2); also elsewhere on the board
/LS8: U1102.8 (D1); also elsewhere on the board
/LS14: U1201.8 (D1); also elsewhere on the board
/MAIN_RLY: U1202.6 (D2); also elsewhere on the board
/PB8_STEP_EN: RN9.8 (R1.2), U1203.2 (1A); also elsewhere on the board
/lowside_quad2/IN1: RN7.8 (R1.2), U1103.2 (1A); also elsewhere on the board
/lowside_quad2/IN2: RN7.7 (R2.2), U1103.5 (2A); also elsewhere on the board
/lowside_quad2/IN3: RN7.6 (R3.2), U1103.9 (3A); also elsewhere on the board
/lowside_quad2/IN4: RN7.5 (R4.2), U1103.12 (4A); also elsewhere on the board
/lowside_quad4/IN2: RN9.7 (R2.2), U1203.5 (2A); also elsewhere on the board
/lowside_quad4/IN3: RN9.6 (R3.2), U1203.9 (3A); also elsewhere on the board
/lowside_quad4/IN4: RN9.5 (R4.2), U1203.12 (4A); also elsewhere on the board
/lowside_quad4/OUT1: U1201.6 (D2)
/lowside_quad4/OUT4: U1202.8 (D1)
unnamed: RN8.1 (R1.1), U1103.11 (4Y)
unnamed: RN8.8 (R1.2), U1102.1 (IN1)
unnamed: RN8.2 (R2.1), U1103.8 (3Y)
unnamed: RN8.7 (R2.2), U1102.3 (IN2)
unnamed: RN8.3 (R3.1), U1103.6 (2Y)
unnamed: RN8.6 (R3.2), U1101.1 (IN1)
unnamed: RN8.4 (R4.1), U1103.3 (1Y)
unnamed: RN8.5 (R4.2), U1101.3 (IN2)
unnamed: RN10.1 (R1.1), U1203.11 (4Y)
unnamed: RN10.8 (R1.2), U1202.1 (IN1)
unnamed: RN10.2 (R2.1), U1203.8 (3Y)
unnamed: RN10.7 (R2.2), U1202.3 (IN2)
unnamed: RN10.3 (R3.1), U1203.6 (2Y)
unnamed: RN10.6 (R3.2), U1201.1 (IN1)
unnamed: RN10.4 (R4.1), U1203.3 (1Y)
unnamed: RN10.5 (R4.2), U1201.3 (IN2)

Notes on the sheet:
Locate output caps near connector pin
